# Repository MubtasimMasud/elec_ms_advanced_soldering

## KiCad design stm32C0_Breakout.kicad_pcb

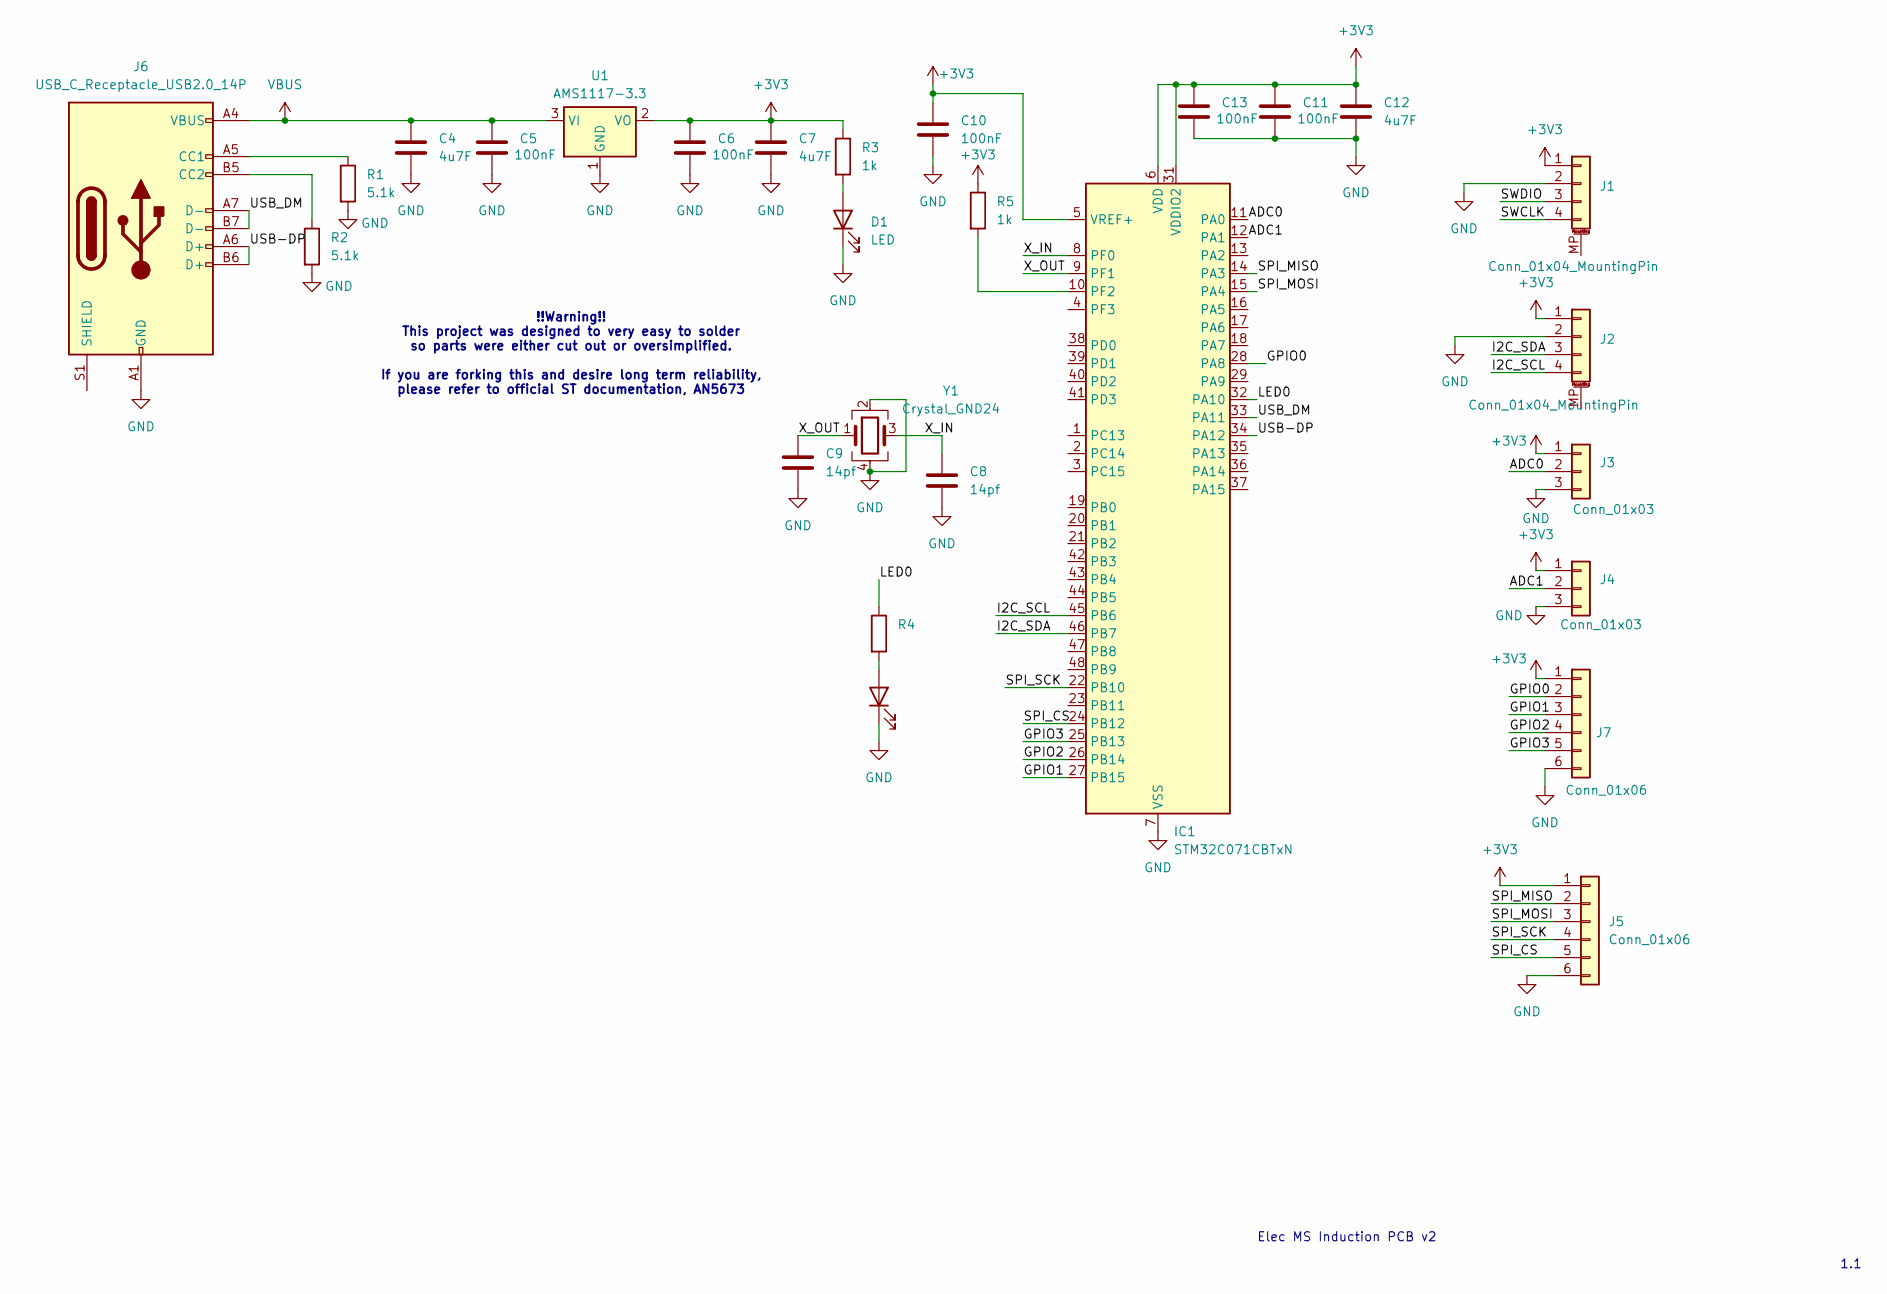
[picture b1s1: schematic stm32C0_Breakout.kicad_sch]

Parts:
C4, C7, C12: 4u7F; C_0805_2012Metric_Pad1.18x1.45mm_HandSolder
C5, C6, C10, C11, C13: 100nF; C_0805_2012Metric_Pad1.18x1.45mm_HandSolder
C8, C9: 14pf; C_0805_2012Metric_Pad1.18x1.45mm_HandSolder
D1, D2: LED; LED_0805_2012Metric_Pad1.15x1.40mm_HandSolder
IC1: STM32C071CBTxN; LQFP-48_7x7mm_P0.5mm
J1, J2: Conn_01x04_MountingPin; PinHeader_1x04_P2.54mm_Vertical
J3, J4: Conn_01x03; PinHeader_1x03_P2.54mm_Vertical
J5, J7: Conn_01x06; PinHeader_1x06_P2.54mm_Vertical
J6: USB_C_Receptacle_USB2.0_14P; USB_C_Receptacle_GCT_USB4105-xx-A_16P_TopMnt_Horizontal
R1, R2: 5.1k; R_0805_2012Metric_Pad1.20x1.40mm_HandSolder
R3, R5: 1k; R_0805_2012Metric_Pad1.20x1.40mm_HandSolder
R4: 100; R_0805_2012Metric_Pad1.20x1.40mm_HandSolder
U1: AMS1117-3.3; SOT-223-3_TabPin2
Y1: Crystal_GND24; Crystal_SMD_3225-4Pin_3.2x2.5mm

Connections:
+3V3: C6.1, C7.1, C10.1, C11.1, C12.1, C13.1, IC1.5 (VREF+), IC1.6 (VDD), IC1.31 (VDDIO2), J1.1, J2.1, J3.1, J4.1, J5.1, J7.1, R3.1, R5.1, U1.2 (VO)
/ADC0: IC1.11 (PA0), J3.2
/ADC1: IC1.12 (PA1), J4.2
/GPIO0: IC1.28 (PA8), J7.2
/GPIO1: IC1.27 (PB15), J7.3
/GPIO2: IC1.26 (PB14), J7.4
/GPIO3: IC1.25 (PB13), J7.5
/I2C_SCL: IC1.45 (PB6), J2.4
/I2C_SDA: IC1.46 (PB7), J2.3
/LED0: IC1.32 (PA10), R4.1
/SPI_CS: IC1.24 (PB12), J5.5
/SPI_MISO: IC1.14 (PA3), J5.2
/SPI_MOSI: IC1.15 (PA4), J5.3
/SPI_SCK: IC1.22 (PB10), J5.4
/SWCLK: J1.4
/SWDIO: J1.3
/USB-DP: IC1.34 (PA12), J6.A6 (D+), J6.B6 (D+)
/USB_DM: IC1.33 (PA11), J6.A7 (D-), J6.B7 (D-)
/X_IN: C8.1, IC1.8 (PF0), Y1.3
/X_OUT: C9.1, IC1.9 (PF1), Y1.1
GND: C4.2, C5.2, C6.2, C7.2, C8.2, C9.2, C10.2, C11.2, C12.2, C13.2, D1.1 (K), D2.1 (K), IC1.7 (VSS), IC1.30 (VSS), J1.2, J2.2, J3.3, J4.3, J5.6, J6.A1 (GND), J6.A12 (GND), J6.B1 (GND), J6.B12 (GND), J7.6, R1.2, R2.2, U1.1 (GND), Y1.2, Y1.4
unnamed: D1.2 (A), R3.2
unnamed: D2.2 (A), R4.2
unnamed: IC1.10 (PF2), R5.2
unnamed: J6.A5 (CC1), R1.1
unnamed: J6.B5 (CC2), R2.1
VBUS: C4.1, C5.1, J6.A4 (VBUS), J6.A9 (VBUS), J6.B4 (VBUS), J6.B9 (VBUS), U1.3 (VI)

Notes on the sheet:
!!Warning!! This project was designed to very easy to solder so parts were either cut out or oversimplified. If you are forking this and desire long term reliability, please refer to official ST documentation, AN5673
Elec MS Induction PCB v2
1.1

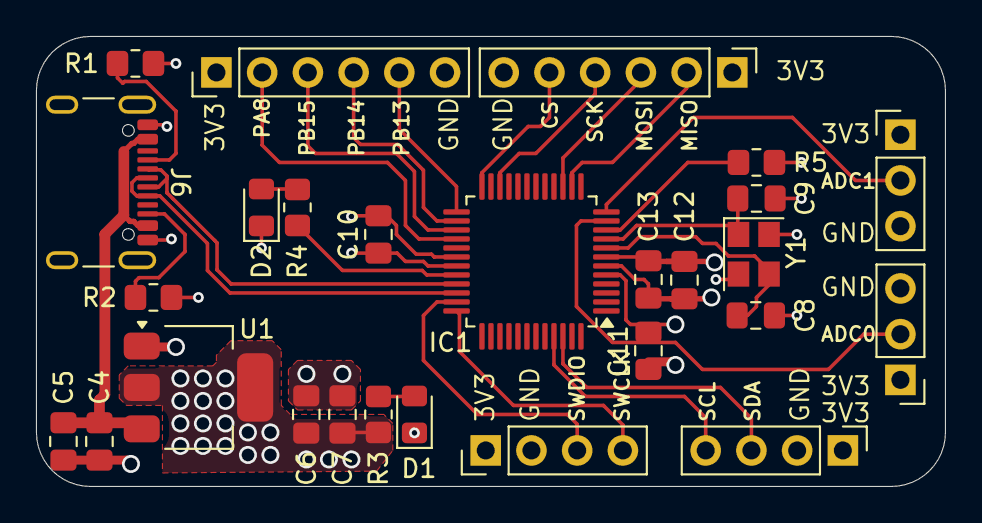
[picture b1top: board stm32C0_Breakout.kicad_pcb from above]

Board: 4 copper layers, 50.5 x 25.0 mm, 27 parts (0 on the bottom side), 25 nets.

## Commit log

2025-05-21 added pcb files
2025-06-22 File dump Oops
